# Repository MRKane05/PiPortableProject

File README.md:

# PiPortableProject

A working repository for the PiPortable project board designed to act as a semi-complete solution for building a raspberry pi portable in the style of a GameBoy.

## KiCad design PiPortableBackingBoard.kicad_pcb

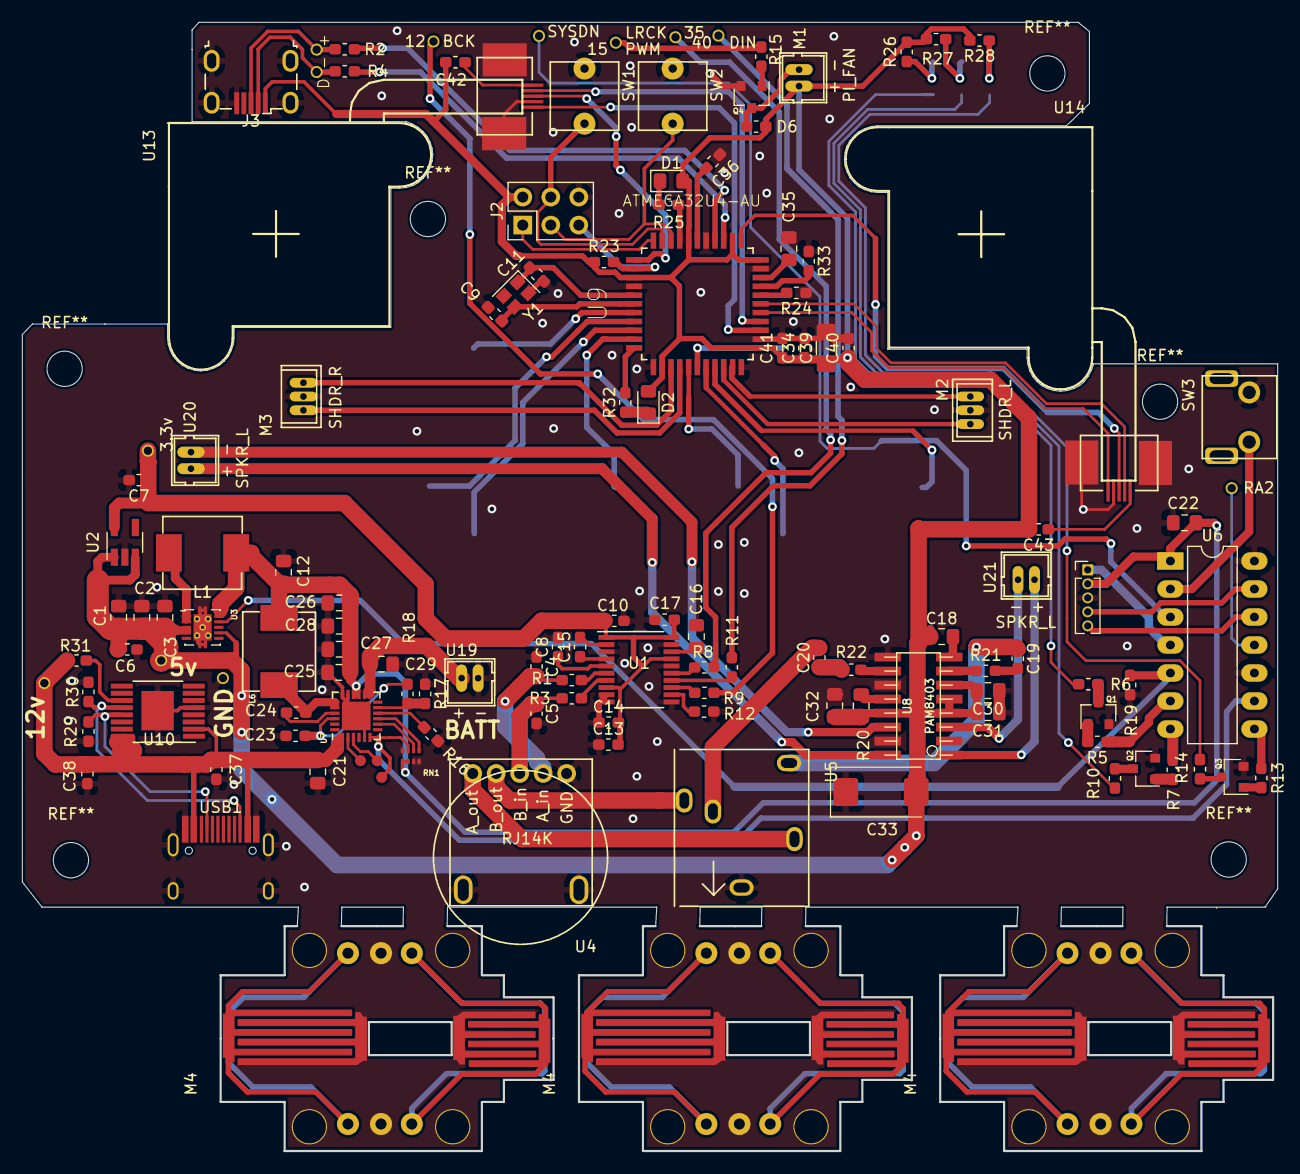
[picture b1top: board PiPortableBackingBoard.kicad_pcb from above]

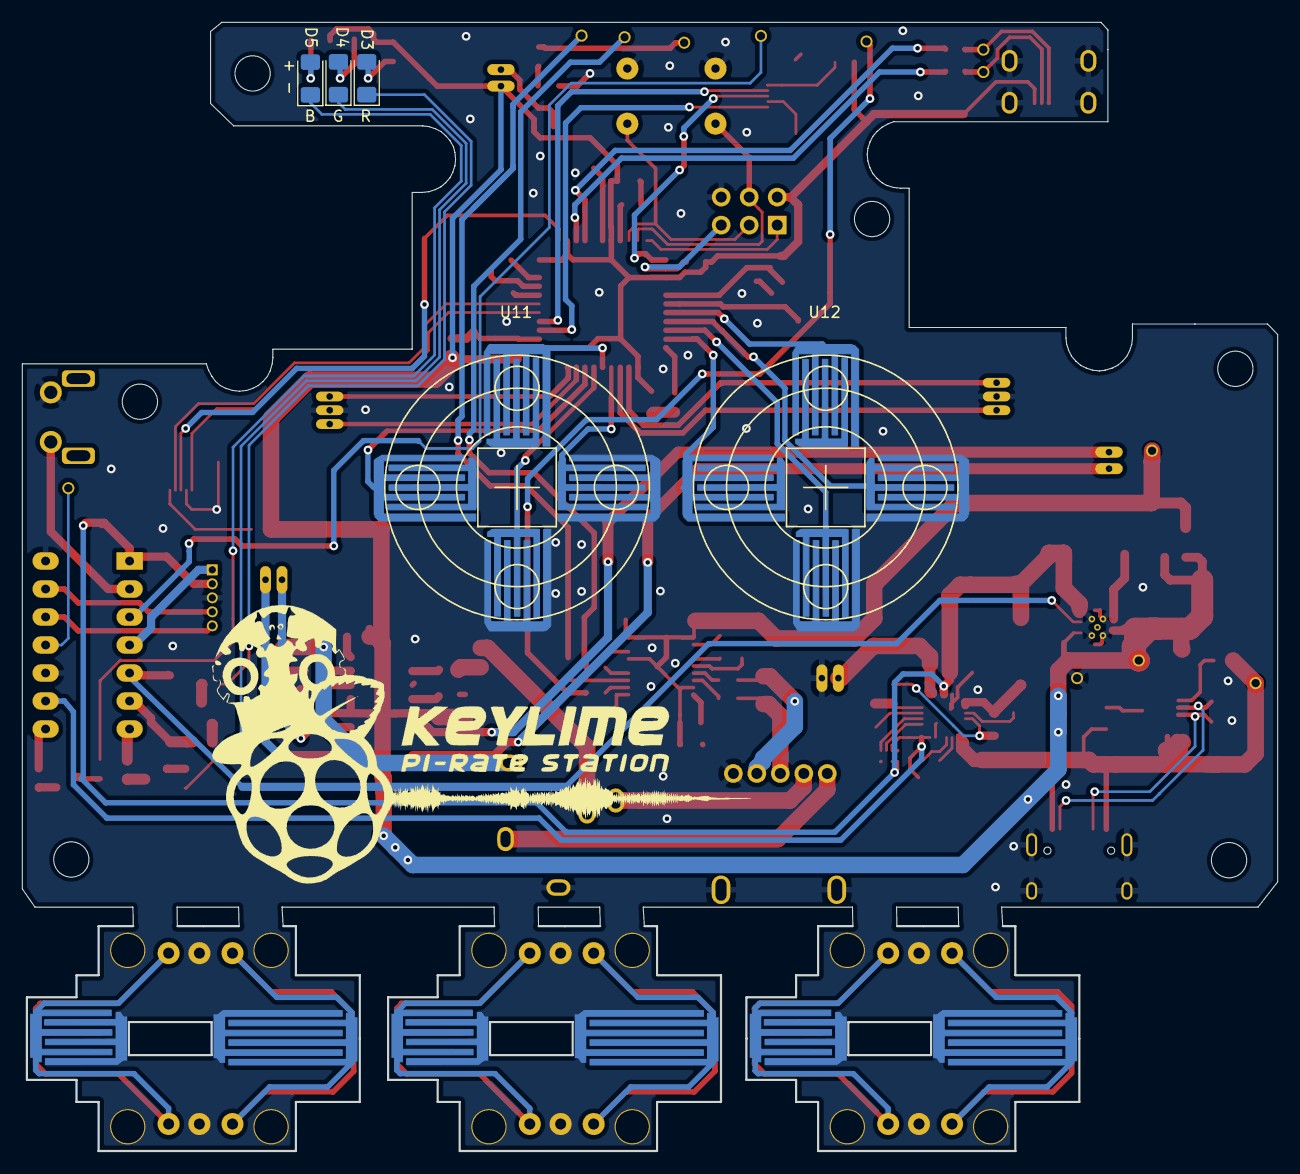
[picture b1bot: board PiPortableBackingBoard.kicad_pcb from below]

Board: 2 copper layers, 113.9 x 102.4 mm, 135 parts (5 on the bottom side), 113 nets.

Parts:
C1, C2, C3, C12: C_22uF; C_0805_2012Metric_Pad1.15x1.40mm_HandSolder
C4, C5: C_2.2NF; C_0603_1608Metric_Pad1.05x0.95mm_HandSolder
C6: C_2.2uF; C_0603_1608Metric_Pad1.05x0.95mm_HandSolder
C7: C_33uF; C_0603_1608Metric_Pad1.05x0.95mm_HandSolder
C8, C15: C_2.2UF; C_0603_1608Metric_Pad1.05x0.95mm_HandSolder
C9, C11: C_22pF; C_0603_1608Metric_Pad1.05x0.95mm_HandSolder
C10: C__0.1UF; C_0603_1608Metric_Pad1.05x0.95mm_HandSolder
C13, C14, C17, C42, C43: C_0.1UF; C_0603_1608Metric_Pad1.05x0.95mm_HandSolder
C16: C_0.1UF; C_0805_2012Metric_Pad1.15x1.40mm_HandSolder
C18, C35: C_0.1uF; C_0805_2012Metric_Pad1.15x1.40mm_HandSolder
C19, C20: C_470nF; C_0603_1608Metric_Pad1.05x0.95mm_HandSolder
C21, C22, C25, C26, C27, C28, C29: C; C_0805_2012Metric_Pad1.15x1.40mm_HandSolder
C23, C24: C; C_0603_1608Metric_Pad1.05x0.95mm_HandSolder
C30, C31, C32: C_1u; C_0805_2012Metric_Pad1.15x1.40mm_HandSolder
C33: CP1_470u; CP_EIA-7343-31_Kemet-D_Pad2.25x2.55mm_HandSolder
C34, C36: C_1.0uF; C_0603_1608Metric_Pad1.05x0.95mm_HandSolder
C37, C40: C_1uF; C_0603_1608Metric_Pad1.05x0.95mm_HandSolder
C38: C_10uF; C_0603_1608Metric_Pad1.05x0.95mm_HandSolder
C39: CP1_10uF; C_1206_3216Metric_Pad1.42x1.75mm_HandSolder
C41: C_0.1uF; C_0603_1608Metric_Pad1.05x0.95mm_HandSolder
D1: LED_YELLOW; LED_0805_2012Metric_Pad1.15x1.40mm_HandSolder
D2: LED_GREEN; LED_0805_2012Metric_Pad1.15x1.40mm_HandSolder
D3: LED_RED; LED_1206_3216Metric_Pad1.42x1.75mm_HandSolder
D4: LED_GREEN; LED_1206_3216Metric_Pad1.42x1.75mm_HandSolder
D5: LED_BLUE; LED_1206_3216Metric_Pad1.42x1.75mm_HandSolder
D6: DIODE; C_0603_1608Metric_Pad1.05x0.95mm_HandSolder
J1, J4, J20: TEST_1P; TP1_THT
J2: PIC_ICSP_6_PIN; PinHeader_2x03_P2.54mm_Vertical
J3: USB_B_Micro; USB_Micro-B_C456008
J6, J7: SYS_DN; TP1_THT
J16, J17, J18: TEST_1P; TP1
J25: Conn_01x05; Pin_Header_Straight_1x05_Pitch1.27mm
L1: L_1uH_5.1A or 8A; ASPI-0630HI-2R2M-T15
L6: L; ASPI-0630HI-2R2M-T15
M1: Fan; JST_1.5_2Pin
M2: SHDR_RIGHT; JST_1.25_3Pin
M3: SHDR_LEFT; JST_1.25_3Pin
M4, M4#2, M4#3: SHDR_BRD; Pi_Shoulders
Q1, Q2, Q3, Q4: 2N3904; SOT-23_custom
R1, R3, R8, R9, R11, R12: R_470; R_0603_1608Metric_Pad1.05x0.95mm_HandSolder
R2, R4: R_22; R_0603_1608Metric_Pad1.05x0.95mm_HandSolder
R5, R7, R13, R16, R17, R18, R19: R; R_0603_1608Metric_Pad1.05x0.95mm_HandSolder
R6, R10, R14, R21, R22, R23, R24, R33: R_10K; R_0603_1608Metric_Pad1.05x0.95mm_HandSolder
R15: R_1K; R_0603_1608Metric_Pad1.05x0.95mm_HandSolder
R20: R_10K; R_0805_2012Metric_Pad1.15x1.40mm_HandSolder
R25, R32: R_330; R_0603_1608Metric_Pad1.05x0.95mm_HandSolder
R26, R27, R28: R_220; R_0603_1608Metric_Pad1.05x0.95mm_HandSolder
R29, R30: R_5.1k; R_0603_1608Metric_Pad1.05x0.95mm_HandSolder
R31: R_100k; R_0603_1608Metric_Pad1.05x0.95mm_HandSolder
RN1: R_Pack04; RA_0804
SW1: START; HardTact
SW2: SELECT; HardTact
SW3: CONTROL; RightAngleTact
TP1: D+; TP1_THT
TP2: D-; TP1_THT
TP4: GND; TP1_THT
TP5: LRCK_GP19; TP1_THT
TP6: DIN_GP40; TP1_THT
TP7: BCK_GP12; TP1_THT
TP8: PWM_GP15; TP1_THT
U1: PCM5102; TSSOP-20_4.4x6.5mm_P0.65mm
U2: SE5218; SOT-23-5_HandSoldering
U3: TPS61230; VSON-10-1EP_3x3mm_Pitch0.5mm_ThermalPad
U4: RJ14K; RJ14K_Modified
U5: PJ30240; AudioJack_PJ30240
U6: PIC_14; DIP-14_W7.62mm_LongPads
U7: bq25895m; QFN-24-1EP_4x4mm_Pitch0.5mm
U8: PAM8403; so-16
U9: ATMEGA32U4-AU; ATmega32U4
U10: IP2721; TSSOP-16-1EP_4.4x5mm_P0.65mm_HandSolder
U11: dPad; PiD-Pad
U12: XOST_Buttons; PiD-Pad
U13: Joycon_R; Switch_Stick_Styler
U14: Joycon_L; Switch_Stick_Styler
U19: BatteryConnector; JST_1.5_2Pin
U20: Audio_R; JST_1.5_2Pin
U21: Audio_L; JST_1.5_2Pin
USB1: HRO-TYPE-C-31-M-12; HRO-TYPE-C-31-M-12-HandSoldering
Y1: SMD CRYSTAL RESONATORS SMD-2520_4P ROHS; Crystal_SMD_2520-4Pin_2.5x2.0mm

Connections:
3v3: C7.1, C10.1, C13.2, C14.2, C17.2, J4.1, U1.1, U1.8, U1.17, U1.20, U2.5
5v: C1.1, C2.1, C3.1, C6.1, C18.1, C30.2, C31.2, C32.2, C33.2, C34.1, C39.1, C40.1, C41.1, C42.2, C43.2, D1.2, D2.2, D6.2, J1.1, J2.2, J3.1, M1.1, R20.1, R23.1, R26.1, R27.1, R28.1, U2.1, U2.3, U3.3, U3.4, U3.7, U8.4, U8.5, U8.6, U8.13, U9.2, U9.7, U9.14, U9.24, U9.34, U9.44
12vSUP: C21.2, C37.2, C38.2, J20.1, R31.1, U7.1, U10.2, U10.16, USB1.2, USB1.11
+OUT_L: U8.1, U21.1
+OUT_R: U8.16, U20.1
-OUT_L: U8.3, U21.2
-OUT_R: U8.14, U20.2
A0: U9.36, U13.5
A1: U9.37, U13.2
A2: U9.38, U14.5
A3: U9.39, U14.2
AT_RESET: J2.5, R23.2, U9.13
BATT: C29.1, U7.13, U7.14, U19.1
BCK: R9.1, TP7.1
BLUE: R13.2, U6.8
CE: RN1.8, U7.9
D0: U9.20, U12.1
D1: U9.21, U12.4
D2: U9.19, U12.3
D3: U9.18, U12.2
D4: M3.1, U9.25
D5: M2.1, U9.31
D7: U9.1, U14.3
D11: U9.12, U13.3
D12: M3.3, U9.26
D13: M2.3, U9.32
D14_MISO: J2.1, U9.11
D15_SCK: J2.3, SW2.1, U9.9
D16_MOSI: J2.4, SW1.1, U9.10
D+: R2.1, U9.4
D-: R4.1, U9.3
DACL: C4.2, R1.2, U4.2
DACR: C5.1, R3.2, U4.3
DDOWN: U9.29, U11.1
DIN: R11.1, TP6.1
DLEFT: U9.30, U11.4
DRIGHT: U9.27, U11.3
DUP: U9.28, U11.2
EN: R19.1, U3.9, U6.5
GREEN: R7.1, U6.7
INL: R21.1, U8.7
INR: R22.1, U8.10
JACKL: U4.5, U5.2
JACKR: U4.4, U5.3
LRCK: R8.1, TP5.1
MCLR: J25.1, U6.4
unnamed: C8.1, U1.5
unnamed: C15.1, U1.4
unnamed: C15.2, U1.2
unnamed: C16.2, U1.18
unnamed: C18.2, U8.8
unnamed: C19.2, R21.2
unnamed: C20.1, R22.2
unnamed: C24.1, L6.2, U7.19, U7.20
unnamed: C24.2, U7.21
unnamed: C35.2, U9.42
unnamed: C36.1, U9.6
unnamed: C42.1, U13.1
unnamed: C43.1, U14.1
unnamed: D1.1, R25.1
unnamed: D2.1, R32.1
unnamed: D3.1, R6.1
unnamed: D3.2, R26.2
unnamed: D4.1, R10.1
unnamed: D4.2, R27.2
unnamed: D5.1, R14.1
unnamed: D5.2, R28.2
unnamed: D6.1, M1.2, Q4.3
unnamed: J3.2, R4.2, TP2.1
unnamed: J3.3, R2.2, TP1.1
unnamed: J6.1, U6.3
unnamed: J7.1, U6.11
unnamed: J17.1, U7.2
unnamed: J18.1, U7.3
unnamed: J25.4, U6.13
unnamed: J25.5, U6.12
unnamed: L1.2, U3.1, U3.2
unnamed: M4.2, M4#2.2, M4#3.2
unnamed: Q1.2, R5.2
unnamed: Q1.3, R6.2
unnamed: Q2.2, R7.2
unnamed: Q2.3, R10.2
unnamed: Q3.2, R13.1
unnamed: Q3.3, R14.2
unnamed: Q4.2, R15.1
unnamed: R1.1, U1.6
unnamed: R3.1, U1.7
unnamed: R8.2, U1.15
unnamed: R9.2, U1.13
unnamed: R11.2, U1.14
unnamed: R12.2, U1.12
unnamed: R16.1, U7.10
unnamed: R17.2, R18.2, U7.11
unnamed: R24.2, U9.40
unnamed: R25.2, U9.8
unnamed: R29.1, U10.13, USB1.4
unnamed: R30.1, U10.12, USB1.10
unnamed: R31.2, U10.11
unnamed: R32.2, U9.22
unnamed: R33.2, U9.41
OTG: RN1.7, U7.8
PAML: C19.1, U5.4
PAMR: C20.2, U5.5
PGND: C1.2, C2.2, C3.2, C4.1, C5.2, C6.2, C7.2, C8.2, C9.1, C10.2, C11.2, C12.1, C13.1, C14.1, C16.1, C17.1, C21.1, C22.1, C23.1, C25.2, C26.1, C27.2, C28.2, C29.2, C30.1, C31.1, C32.1, C33.1, C34.2, C35.1, C36.2, C37.1, C38.1, C39.2, C40.2, C41.2, J2.6, J3.5, J3.6, J25.3, M2.2, M3.2, M4.1, M4#2.1, M4#3.1, Q1.1, Q2.1, Q3.1, Q4.1, R12.1, R16.2, R17.1, R19.2, R24.1, R29.2, R30.2, R33.1, RN1.1, RN1.2, RN1.5, SW1.2, SW2.2, SW3.1, TP4.1, U1.3, U1.9, U1.10, U1.11, U1.16, U1.19, U2.2, U3.11, U4.1, U5.1, U6.10, U6.14, U7.5, U7.17, U7.18, U7.25, U8.2, U8.9, U8.11, U8.15, U9.5, U9.15, U9.23, U9.33, U9.35, U9.43, U10.5, U11.0, U12.0, U13.4, U14.4, U19.2, USB1.1, USB1.12, USB1.13, Y1.2, Y1.4
PWMCtrl: R15.2, TP8.1
RED: R5.1, U6.6
REGN: C23.2, R18.1, U7.22
SDA: J16.1, RN1.6, U6.9, U7.6
SHND: R20.2, U8.12
VSYS: C12.2, C22.2, C25.1, C26.2, C27.1, C28.1, J25.2, L1.1, L6.1, RN1.3, RN1.4, U3.10, U6.1, U7.15, U7.16
XTAL1: C9.2, U9.17, Y1.3
XTAL2: C11.1, U9.16, Y1.1
button: SW3.2, U6.2

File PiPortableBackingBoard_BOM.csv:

"Id";"Designator";"Package";"Quantity";"Designation";"Supplier and ref";
1;"U11";"PiD-Pad";1;"dPad";;;
2;"U12";"PiD-Pad";1;"XOST_Buttons";;;
3;"M4,M5";"Pi_Shoulders";2;"SHDR_BRD";;;
4;"U13";"Switch_Stick";1;"Joycon_R";;;
5;"U14";"Switch_Stick";1;"Joycon_L";;;
6;"REF**,REF**,REF**,REF**,REF**,REF**";"MountingHole_3.2mm_M3";6;"MountingHole_3.2mm_M3";;;
7;"J17,J16,J18,J14";"TP1";4;"TEST_1P";;;
8;"C1,C2,C3,C12";"C_0805_2012Metric_Pad1.15x1.40mm_HandSolder";4;"C_22uF";;;
9;"C21,C22,C25,C26,C27,C28,C29";"C_0805_2012Metric_Pad1.15x1.40mm_HandSolder";7;"C";;;
10;"J25";"Pin_Header_Straight_1x05_Pitch1.27mm";1;"Conn_01x05";;;
11;"L6";"ASPI-0630HI-2R2M-T15";1;"L";;;
12;"Q1,Q2,Q3,Q4";"SOT-23_custom";4;"2N3904";;;
13;"RN1";"RA_0804";1;"R_Pack04";;;
14;"U3";"VSON-10-1EP_3x3mm_Pitch0.5mm_ThermalPad";1;"TPS61230";;;
15;"U6";"UQFN-16-1EP_4x4mm_Pitch0.65mm";1;"PIC16F15324";;;
16;"U7";"QFN-24-1EP_4x4mm_Pitch0.5mm";1;"bq25895m";;;
17;"C16";"C_0805_2012Metric_Pad1.15x1.40mm_HandSolder";1;"C_0.1UF";;;
18;"C18,C35";"C_0805_2012Metric_Pad1.15x1.40mm_HandSolder";2;"C_0.1uF";;;
19;"C30,C31,C32";"C_0805_2012Metric_Pad1.15x1.40mm_HandSolder";3;"C_1u";;;
20;"U1";"TSSOP-20_4.4x6.5mm_P0.65mm";1;"PCM5102";;;
21;"U4";"RJ14K_Modified";1;"RJ14K";;;
22;"U5";"AudioJack_PJ30240";1;"PJ30240";;;
23;"U8";"so-16";1;"PAM8403";;;
24;"R1,R3,R8,R9,R11,R12";"R_0603_1608Metric_Pad1.05x0.95mm_HandSolder";6;"R_470";;;
25;"R5,R7,R13,R16,R17,R18,R19";"R_0603_1608Metric_Pad1.05x0.95mm_HandSolder";7;"R";;;
26;"R6,R10,R14,R21,R22,R23,R24,R33";"R_0603_1608Metric_Pad1.05x0.95mm_HandSolder";8;"R_10K";;;
27;"C7";"C_0805_2012Metric_Pad1.15x1.40mm_HandSolder";1;"C_33uF";;;
28;"D3";"LED_1206_3216Metric_Pad1.42x1.75mm_HandSolder";1;"LED_RED";;;
29;"D4";"LED_1206_3216Metric_Pad1.42x1.75mm_HandSolder";1;"LED_GREEN";;;
30;"D5";"LED_1206_3216Metric_Pad1.42x1.75mm_HandSolder";1;"LED_BLUE";;;
31;"R2,R4";"R_0603_1608Metric_Pad1.05x0.95mm_HandSolder";2;"R_22";;;
32;"TP1";"TP1_THT";1;"D+";;;
33;"TP2";"TP1_THT";1;"D-";;;
34;"U2";"TI_National_Semiconductor-LM3940IMP-3.3-Level_A";1;"LM3940IMP-3.3";;;
35;"R26,R27,R28";"R_0603_1608Metric_Pad1.05x0.95mm_HandSolder";3;"R_220";;;
36;"R25,R32";"R_0603_1608Metric_Pad1.05x0.95mm_HandSolder";2;"R_330";;;
37;"R29,R30";"R_0603_1608Metric_Pad1.05x0.95mm_HandSolder";2;"R_5.1k";;;
38;"R31";"R_0603_1608Metric_Pad1.05x0.95mm_HandSolder";1;"R_100k";;;
39;"U9";"ATmega32U4";1;"ATMEGA32U4-AU";;;
40;"TP4";"TP1_THT";1;"GND";;;
41;"TP5";"TP1_THT";1;"LRCK_GP19";;;
42;"TP6";"TP1_THT";1;"DIN_GP40";;;
43;"TP7";"TP1_THT";1;"BCK_GP12";;;
44;"U10";"TSSOP-16-1EP_4.4x5mm_P0.65mm_HandSolder";1;"IP2721";;;
45;"USB1";"HRO-TYPE-C-31-M-12-HandSoldering";1;"HRO-TYPE-C-31-M-12";;;
46;"M1";"JST_1.5_2Pin";1;"Fan";;;
47;"R15";"R_0603_1608Metric_Pad1.05x0.95mm_HandSolder";1;"R_1K";;;
48;"TP8";"TP1_THT";1;"PWM_GP15";;;
49;"Y1";"Crystal_SMD_2520-4Pin_2.5x2.0mm";1;"SMD CRYSTAL RESONATORS SMD-2520_4P ROHS";;;
50;"C33";"CP_EIA-7343-31_Kemet-D_Pad2.25x2.55mm_HandSolder";1;"CP1_470u";;;
51;"C19,C20";"C_0603_1608Metric_Pad1.05x0.95mm_HandSolder";2;"C_470nF";;;
52;"C4,C5";"C_0603_1608Metric_Pad1.05x0.95mm_HandSolder";2;"C_2.2NF";;;
53;"C6";"C_0603_1608Metric_Pad1.05x0.95mm_HandSolder";1;"C_0.47uF";;;
54;"C8,C15";"C_0603_1608Metric_Pad1.05x0.95mm_HandSolder";2;"C_2.2UF";;;
55;"C9,C11";"C_0603_1608Metric_Pad1.05x0.95mm_HandSolder";2;"C_22pF";;;
56;"C10";"C_0603_1608Metric_Pad1.05x0.95mm_HandSolder";1;"C__0.1UF";;;
57;"C13,C14,C17,C42,C43";"C_0603_1608Metric_Pad1.05x0.95mm_HandSolder";5;"C_0.1UF";;;
58;"C23,C24";"C_0603_1608Metric_Pad1.05x0.95mm_HandSolder";2;"C";;;
59;"C34,C36";"C_0603_1608Metric_Pad1.05x0.95mm_HandSolder";2;"C_1.0uF";;;
60;"C37,C40";"C_0603_1608Metric_Pad1.05x0.95mm_HandSolder";2;"C_1uF";;;
61;"C39";"C_1206_3216Metric_Pad1.42x1.75mm_HandSolder";1;"CP1_10uF";;;
62;"C41";"C_0603_1608Metric_Pad1.05x0.95mm_HandSolder";1;"C_0.1uF";;;
63;"D1";"LED_0805_2012Metric_Pad1.15x1.40mm_HandSolder";1;"LED_YELLOW";;;
64;"D2";"LED_0805_2012Metric_Pad1.15x1.40mm_HandSolder";1;"LED_GREEN";;;
65;"D6";"C_0603_1608Metric_Pad1.05x0.95mm_HandSolder";1;"DIODE";;;
66;"J2";"PinHeader_2x03_P2.54mm_Vertical";1;"PIC_ICSP_6_PIN";;;
67;"J3";"USB_Micro-B_C456008";1;"USB_B_Micro";;;
68;"L1";"L_Vishay_IHLP-2020";1;"L_1uH_5.1A";;;
69;"R20";"R_0805_2012Metric_Pad1.15x1.40mm_HandSolder";1;"R_10K";;;
70;"U19";"JST_1.5_2Pin";1;"BatteryConnector";;;
71;"U20";"JST_1.5_2Pin";1;"Audio_R";;;
72;"U21";"JST_1.5_2Pin";1;"Audio_L";;;
73;"C38";"C_0603_1608Metric_Pad1.05x0.95mm_HandSolder";1;"C_10uF";;;
74;"M2";"JST_1.25_3Pin";1;"SHDR_RIGHT";;;
75;"M3";"JST_1.25_3Pin";1;"SHDR_LEFT";;;
76;"SW1";"HardTact";1;"START";;;
77;"SW2";"HardTact";1;"SELECT";;;
78;"J20,J1,J4";"TP1_THT";3;"TEST_1P";;;
79;"SW3";"RightAngleTact";1;"CONTROL";;;
